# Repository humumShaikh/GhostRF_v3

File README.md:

NRF based wireless device

Consists of 4 NRF24L01+ transceivers paired with a single ESP32 SoC for wireless applications

[schematic.pdf](https://github.com/user-attachments/files/23459988/schematic.pdf)

**Final Prototype**

**Connections**

The connections are made through an enamel coated or insulated copper wire.

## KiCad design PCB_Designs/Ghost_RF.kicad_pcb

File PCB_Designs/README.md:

NOTE - This pcb design is not the same as the one show in the photos
       This is for reference only and as a concept

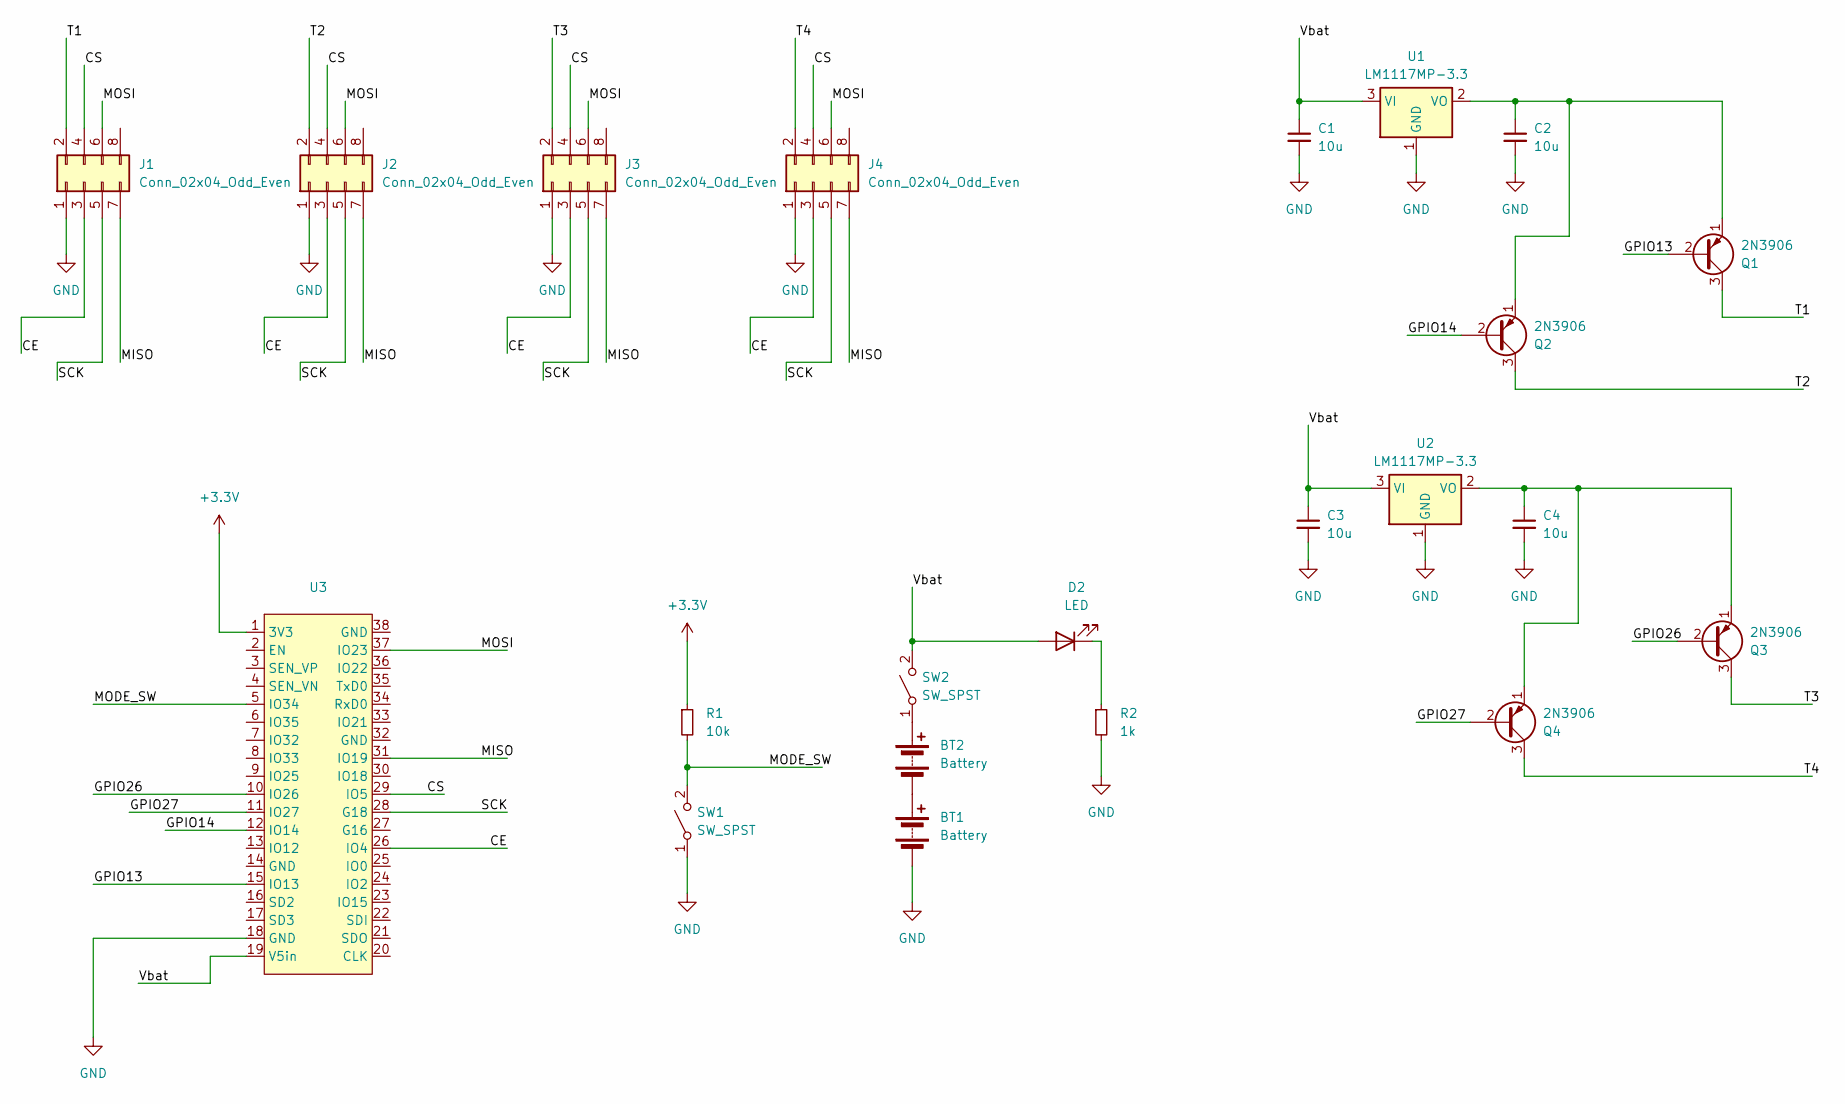
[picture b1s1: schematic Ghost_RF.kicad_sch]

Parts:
BT1, BT2: Battery; BatteryHolder_Keystone_1042_1x18650
C1, C2, C3, C4: 10u; CAP_NP
D2: LED; LED_D3.0mm
J1, J2, J3, J4: Conn_02x04_Odd_Even; PinHeader_2x04_P2.54mm_Vertical
Q1, Q2, Q3, Q4: 2N3906; TO-92_Inline
R1: 10k; R
R2: 1k; R
SW1, SW2: SW_SPST; SW_Slide_SPDT_Straight_CK_OS102011MS2Q
U1, U2: LM1117MP-3.3; SOT-223-3_TabPin2
U3: ESP32S_AITHINKER_DEV_BRD

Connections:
+3.3V: R1.1, U3.1 (3V3)
/CE: J1.3, J2.3, J3.3, J4.3, U3.26 (IO4)
/CS: J1.4, J2.4, J3.4, J4.4, U3.29 (IO5)
/GPIO13: Q1.2 (B), U3.15 (IO13)
/GPIO14: Q2.2 (B), U3.12 (IO14)
/GPIO26: Q3.2 (B), U3.10 (IO26)
/GPIO27: Q4.2 (B), U3.11 (IO27)
/MISO: J1.7, J2.7, J3.7, J4.7, U3.31 (IO19)
/MODE_SW: R1.2, SW1.2 (B), U3.5 (IO34)
/MOSI: J1.6, J2.6, J3.6, J4.6, U3.37 (IO23)
/SCK: J1.5, J2.5, J3.5, J4.5, U3.28 (G18)
/T1: J1.2, Q1.3 (C)
/T2: J2.2, Q2.3 (C)
/T3: J3.2, Q3.3 (C)
/T4: J4.2, Q4.3 (C)
/Vbat: C1.1, C3.1, D2.2 (A), SW2.2 (B), U1.3 (VI), U2.3 (VI), U3.19 (V5in)
GND: BT1.2 (-), C1.2, C2.2, C3.2, C4.2, J1.1, J2.1, J3.1, J4.1, R2.2, SW1.1 (A), U1.1 (GND), U2.1 (GND), U3.18 (GND)
unnamed: BT1.1 (+), BT2.2 (-)
unnamed: BT2.1 (+), SW2.1 (A)
unnamed: D2.1 (K), R2.1
unnamed: C2.1, Q1.1 (E), Q2.1 (E), U1.2 (VO)
unnamed: C4.1, Q3.1 (E), Q4.1 (E), U2.2 (VO)

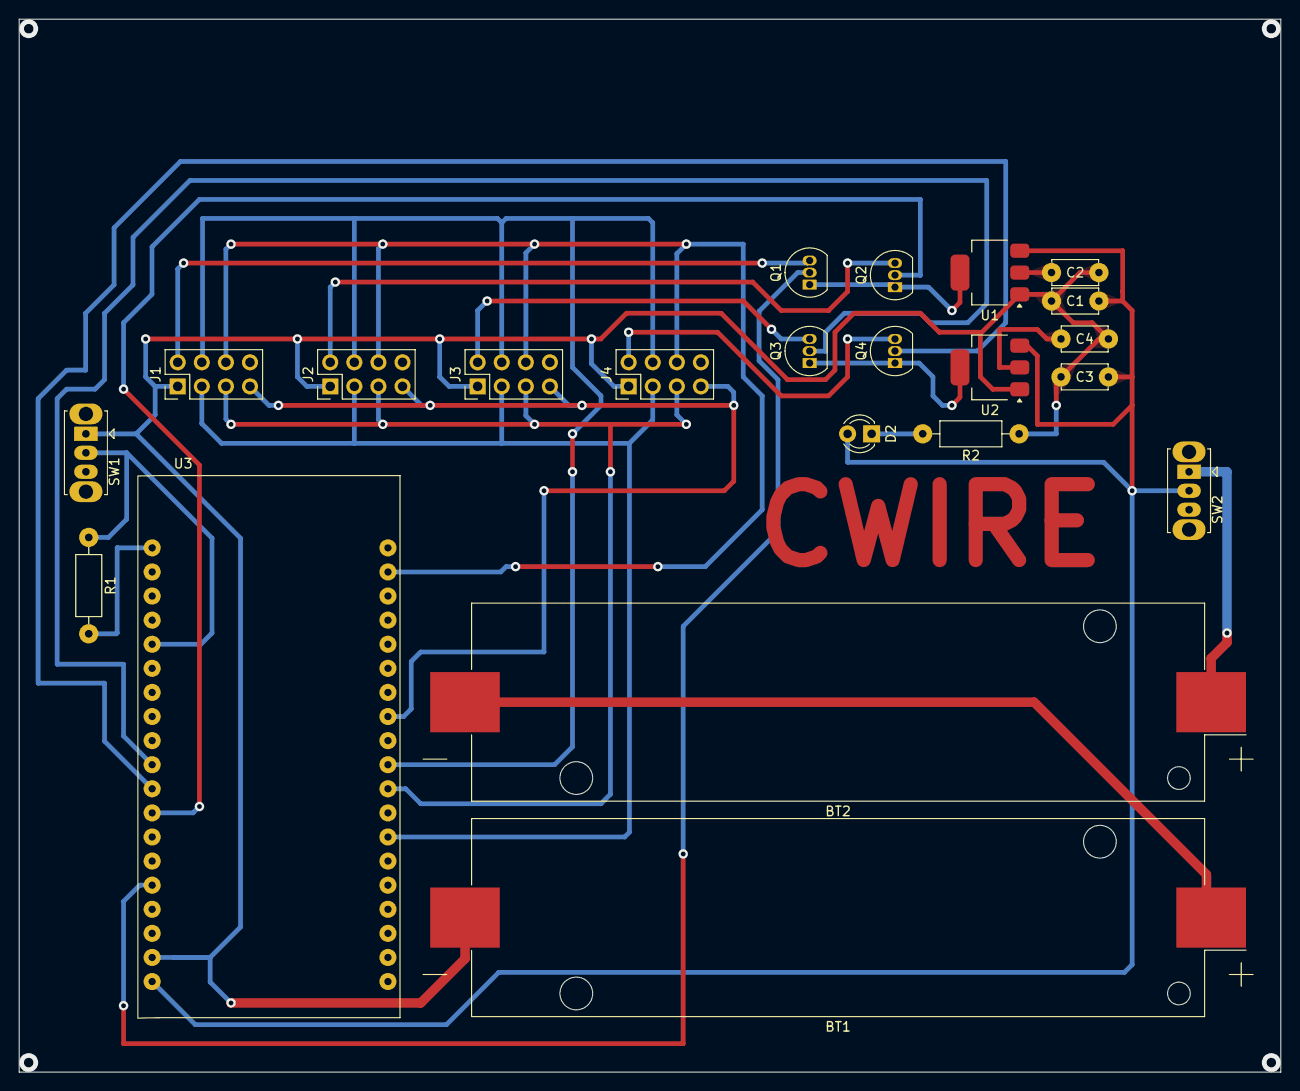
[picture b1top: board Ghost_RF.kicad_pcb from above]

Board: 2 copper layers, 133.0 x 111.0 mm, 22 parts (0 on the bottom side), 22 nets.
